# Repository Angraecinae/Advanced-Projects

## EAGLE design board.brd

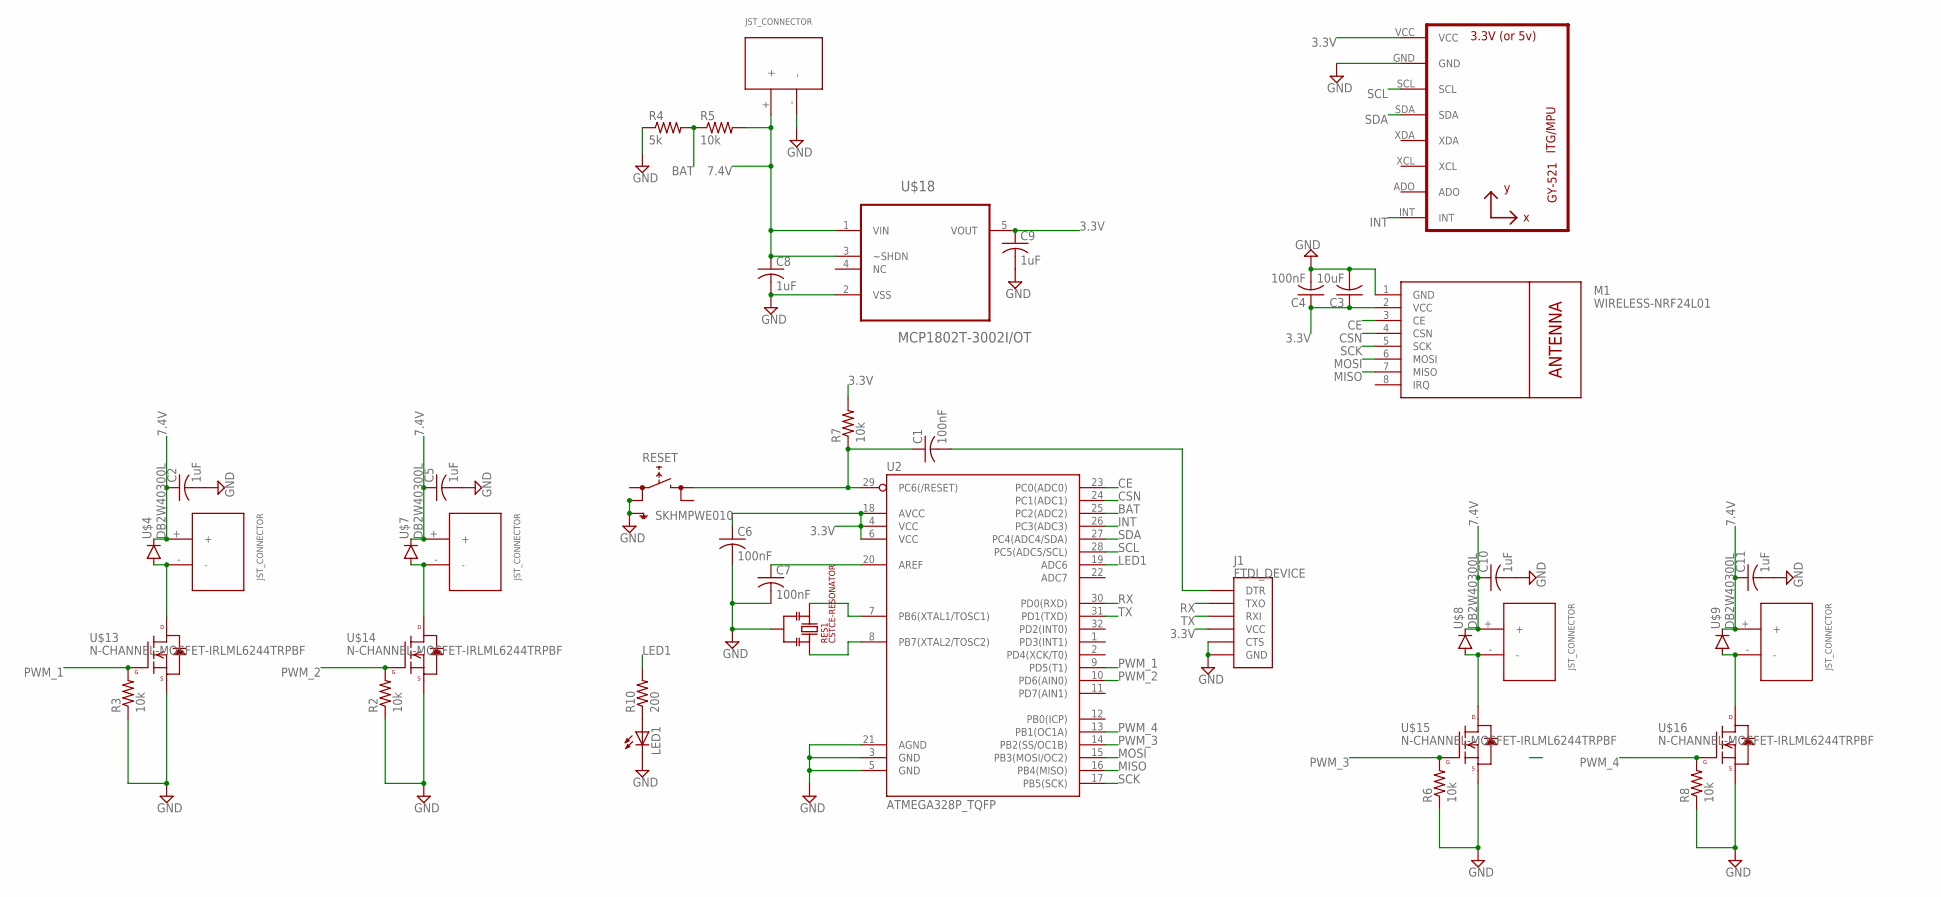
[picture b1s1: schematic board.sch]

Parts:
C1, C4, C6, C7: 100nF; C0603
C2, C5, C8, C9, C10, C11: 1uF; C0603
C3: 10uF; C0603
J1: FTDI_DEVICE; FTDI_DEVICE_SIDE
LED1: LEDCHIP-LED0603; CHIP-LED0603
M1: WIRELESS-NRF24L01
R2, R3, R5, R6, R7, R8: 10k; R0603
R4: 5k; R0603
R10: 200; R0603
RES1: CSTCE-RESONATOR; CSTCE16M0V53-R0
RESET: SKHMPWE010; SKHMPXE010
U1: GY-521MPU6050; GY-521
U2: ATMEGA328P_TQFP; TQFP32-08
U$3, U$10, U$11, U$12, U$17: JST_CONNECTOR_FEMALE
U$4, U$7, U$8, U$9: DB2W40300L; MINI2-F3-B
U$13, U$14, U$15, U$16: N-CHANNEL-MOSFET-IRLML6244TRPBF; SOT23-3
U$18: MCP1802T-3002I/OT; SOT95P270X145-5N

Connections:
3.3V: C3.1, C4.1, C6.1, C9.1, J1.P$4 (VCC), M1.2 (VCC), R7.2, U1.VCC, U2.4 (VCC), U2.6 (VCC), U2.18 (AVCC), U$18.5 (VOUT)
7.4V: C2.1, C5.1, C8.1, C10.1, C11.1, R5.2, U$3.+, U$4.NEG (GPIN), U$7.NEG (GPIN), U$8.NEG (GPIN), U$9.NEG (GPIN), U$10.+, U$11.+, U$12.+, U$17.+, U$18.1 (VIN), U$18.3 (~SHDN)
BAT: R4.2, R5.1, U2.25 (PC2(ADC2))
CE: M1.3 (CE), U2.23 (PC0(ADC0))
CSN: M1.4 (CSN), U2.24 (PC1(ADC1))
GND: C2.2, C3.2, C4.2, C5.2, C6.2, C7.2, C8.2, C9.2, C10.2, C11.2, J1.P$5 (CTS), J1.P$6 (GND), LED1.C, M1.1 (GND), R2.1, R3.1, R4.1, R6.1, R8.1, RES1.P$2, RESET.2 (1.2), RESET.5 (SH), U1.GND, U2.3 (GND), U2.5 (GND), U2.21 (AGND), U$13.2 (S), U$14.2 (S), U$15.2 (S), U$16.2 (S), U$17.-, U$18.2 (VSS)
INT: U1.INT, U2.26 (PC3(ADC3))
LED1: R10.2, U2.19 (ADC6)
MISO: M1.7 (MISO), U2.16 (PB4(MISO))
MOSI: M1.6 (MOSI), U2.15 (PB3(MOSI/OC2))
unnamed: RES1.P$3, U2.7 (PB6(XTAL1/TOSC1))
unnamed: RES1.P$1, U2.8 (PB7(XTAL2/TOSC2))
unnamed: U$8.POS (PPIN), U$11.-, U$15.3 (D)
unnamed: LED1.A, R10.1
unnamed: C7.1, U2.20 (AREF)
unnamed: C1.1, R7.1, RESET.3 (2.1), U2.29 (PC6(/RESET))
unnamed: C1.2, J1.P$1 (DTR)
unnamed: U$3.-, U$4.POS (PPIN), U$13.3 (D)
unnamed: U$7.POS (PPIN), U$10.-, U$14.3 (D)
unnamed: U$9.POS (PPIN), U$12.-, U$16.3 (D)
PWM_1: R3.2, U2.9 (PD5(T1)), U$13.1 (G)
PWM_2: R2.2, U2.10 (PD6(AIN0)), U$14.1 (G)
PWM_3: R6.2, U2.14 (PB2(SS/OC1B)), U$15.1 (G)
PWM_4: R8.2, U2.13 (PB1(OC1A)), U$16.1 (G)
RX: J1.P$2 (TXO), U2.30 (PD0(RXD))
SCK: M1.5 (SCK), U2.17 (PB5(SCK))
SCL: U1.SCL, U2.28 (PC5(ADC5/SCL))
SDA: U1.SDA, U2.27 (PC4(ADC4/SDA))
TX: J1.P$3 (RXI), U2.31 (PD1(TXD))

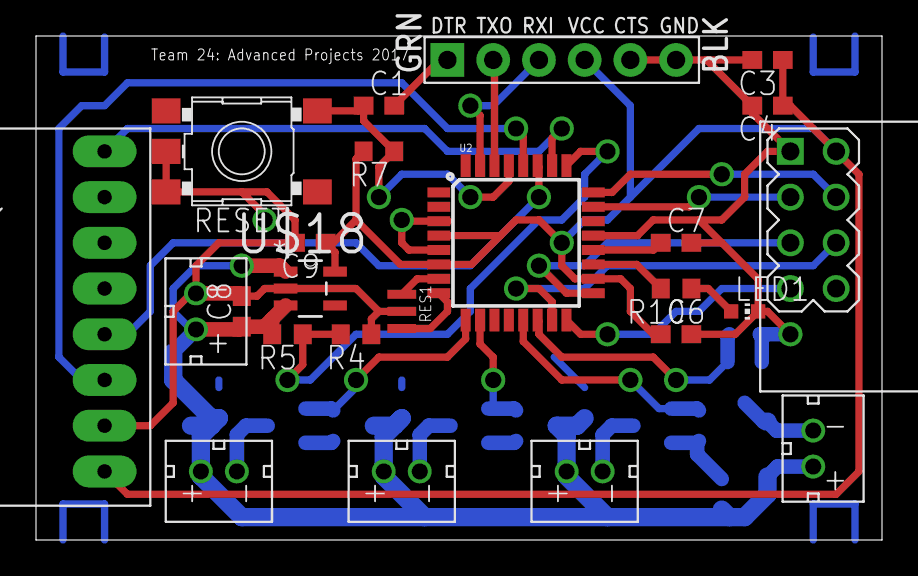
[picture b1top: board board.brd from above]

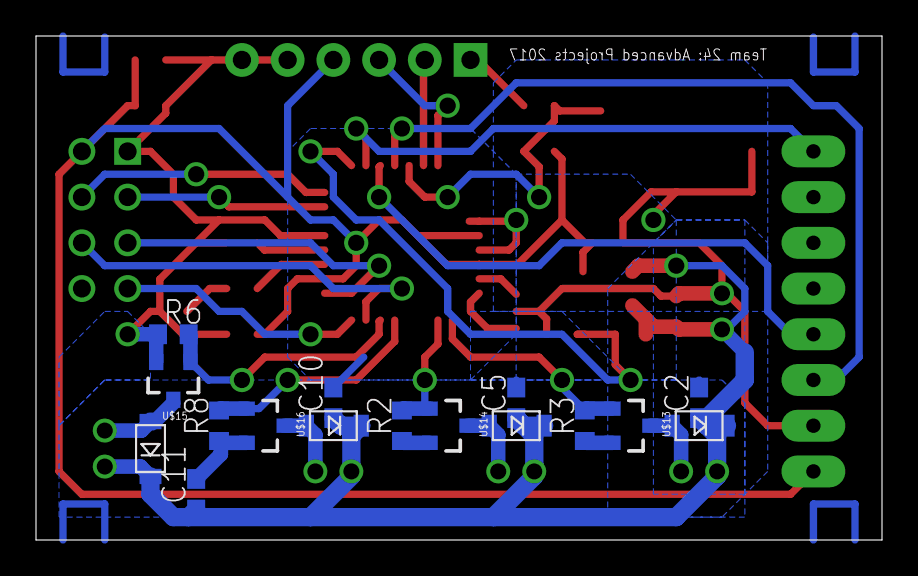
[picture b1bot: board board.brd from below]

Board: 2 copper layers, 47.0 x 28.0 mm, 40 parts (16 on the bottom side), 29 nets.
